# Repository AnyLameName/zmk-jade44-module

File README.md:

# Jade44 - A ZMK Keyboard Module

The Jade44 keyboard is a bespoke keyboard, designed for a userbase of one. 
This repository contains a module for the [ZMK Firmware](https://zmk.dev/) Project that will enable you to build
a firmware for the Jade44.

It also defines a GitHub Actions Workflow that will automatically build the firmware when a change is pushed.

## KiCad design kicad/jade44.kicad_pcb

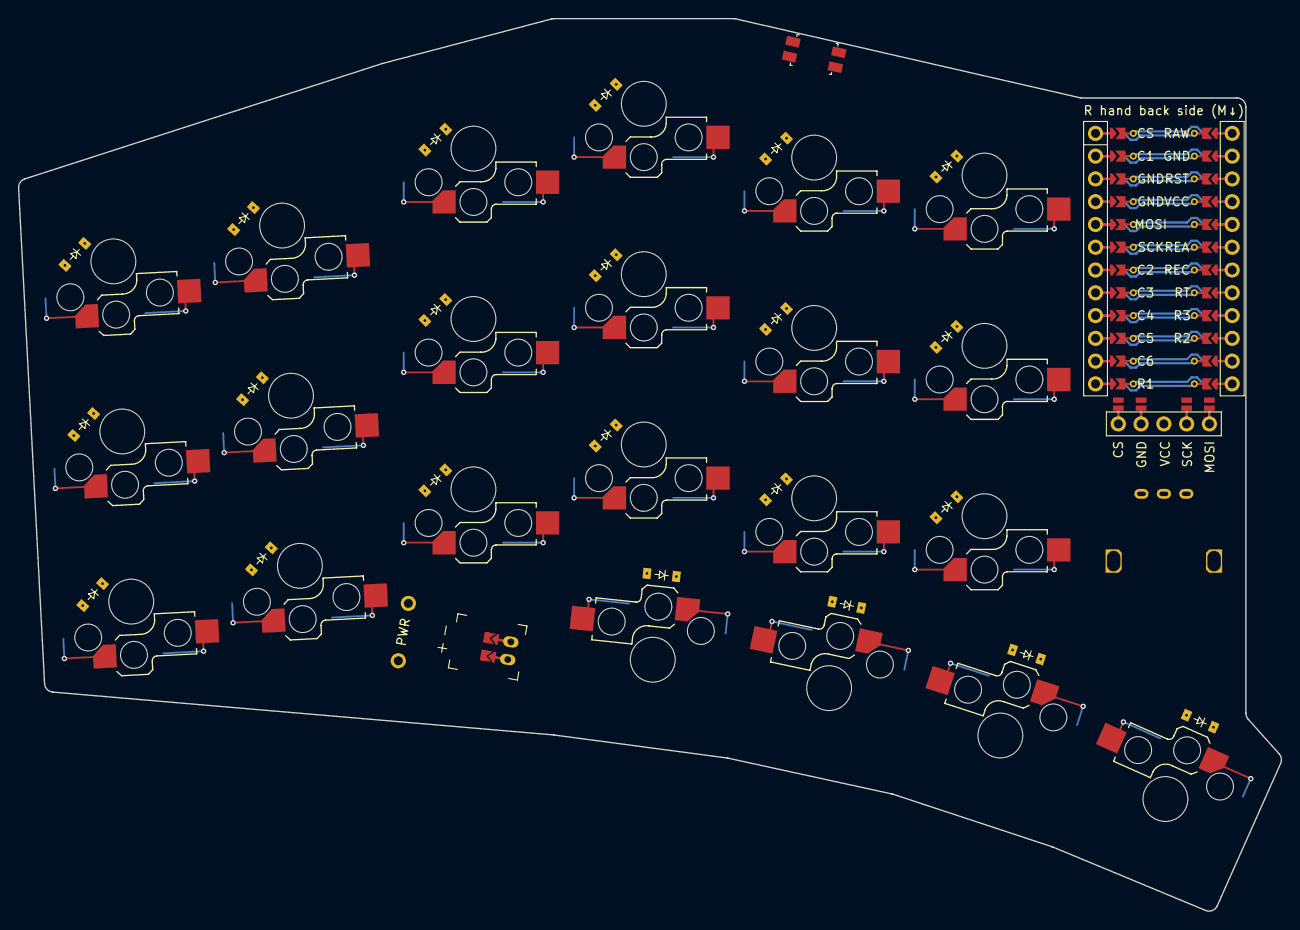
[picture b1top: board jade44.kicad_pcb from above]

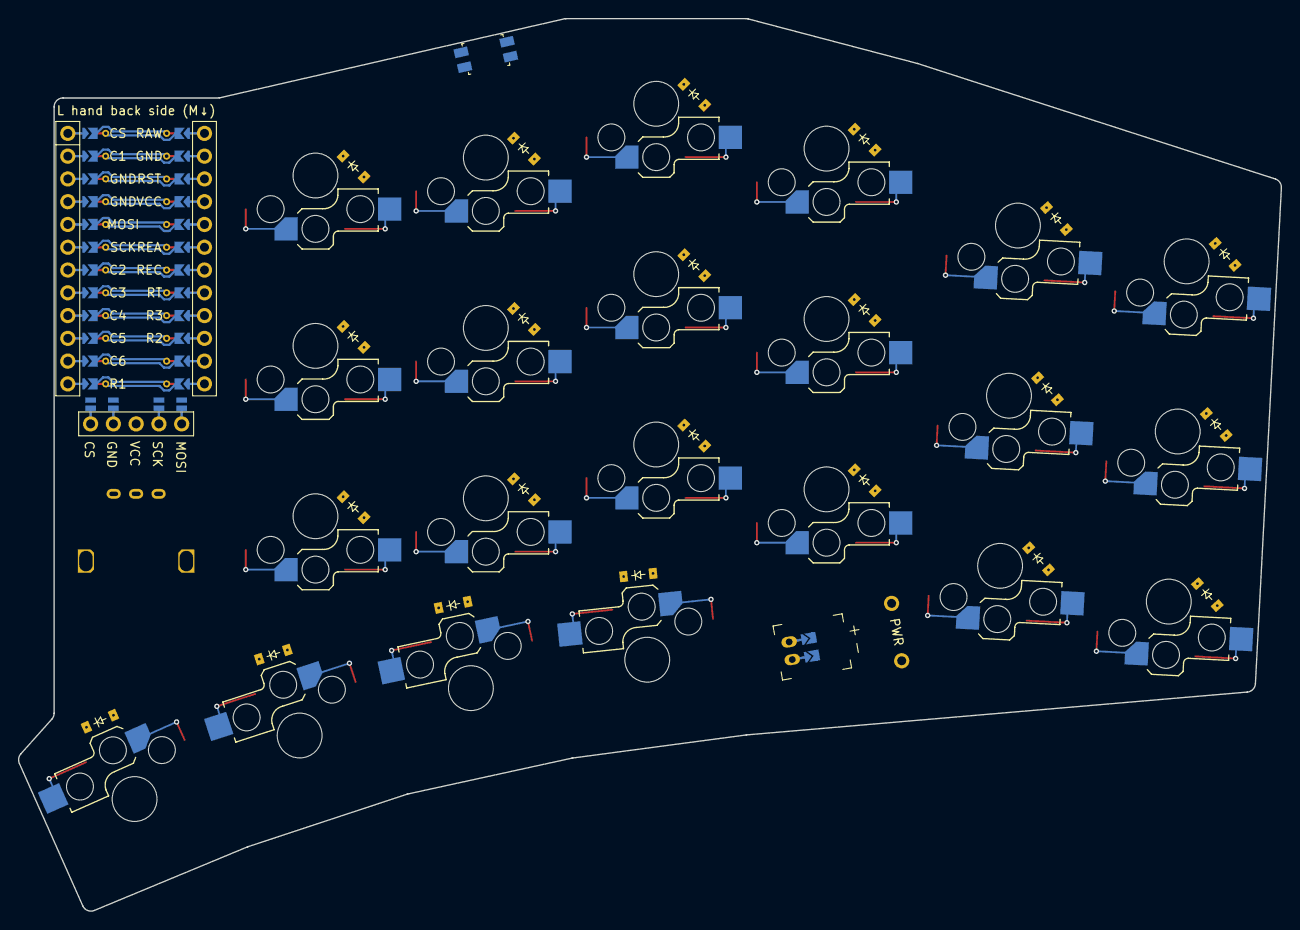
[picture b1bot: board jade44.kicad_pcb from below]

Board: 2 copper layers, 140.8 x 99.5 mm, 50 parts (25 on the bottom side), 48 nets.

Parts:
D1, D2, D3, D4, D5, D6, D7, D8, D9, D10, D11, D12, D13, D14, D15, D16, D17, D18, D19, D20, D21, D22: diode_tht_sod123
DISP1: display_nice_view
JST1: battery_connector_jst_ph_2
MCU1: mcu_nice_nano
PWR1: reset_switch_tht_top
RE1: rotary_encoder_ec11_ec12
RST1: reset_switch_smd_side
S1, S2, S3, S4, S5, S6, S7, S8, S9, S10, S11, S12, S13, S14, S15, S16, S17, S18, S19, S20, S21, S22: switch_choc_v1_v2

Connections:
BAT_P: JST1.1, PWR1.2
C1: MCU1.123, S1.1, S1.2, S2.1, S2.2, S3.1, S3.2
C1_R1: D1.2, S1.1, S1.2
C1_R2: D2.2, S2.1, S2.2
C1_R3: D3.2, S3.1, S3.2
C2: MCU1.118, S4.1, S4.2, S5.1, S5.2, S6.1, S6.2
C2_R1: D4.2, S4.1, S4.2
C2_R2: D5.2, S5.1, S5.2
C2_R3: D6.2, S6.1, S6.2
C3: MCU1.117, S7.1, S7.2, S8.1, S8.2, S9.1, S9.2, S19.1, S19.2
C3_R1: D7.2, S7.1, S7.2
C3_R2: D8.2, S8.1, S8.2
C3_R3: D9.2, S9.1, S9.2
C3_RT: D19.2, S19.1, S19.2
C4: MCU1.116, S10.1, S10.2, S11.1, S11.2, S12.1, S12.2, S20.1, S20.2
C4_R1: D10.2, S10.1, S10.2
C4_R2: D11.2, S11.1, S11.2
C4_R3: D12.2, S12.1, S12.2
C4_RT: D20.2, S20.1, S20.2
C5: MCU1.115, S13.1, S13.2, S14.1, S14.2, S15.1, S15.2, S21.1, S21.2
C5_R1: D13.2, S13.1, S13.2
C5_R2: D14.2, S14.1, S14.2
C5_R3: D15.2, S15.1, S15.2
C5_RT: D21.2, S21.1, S21.2
C6: MCU1.114, S16.1, S16.2, S17.1, S17.2, S18.1, S18.2, S22.1, S22.2
C6_R1: D16.2, S16.1, S16.2
C6_R2: D17.2, S17.1, S17.2
C6_R3: D18.2, S18.1, S18.2
C6_RT: D22.2, S22.1, S22.2
CS: DISP1.14, DISP1.24, MCU1.124
DISP1_1: DISP1.1, DISP1.10, DISP1.23
DISP1_2: DISP1.2, DISP1.11, DISP1.22
DISP1_4: DISP1.4, DISP1.12, DISP1.21
DISP1_5: DISP1.5, DISP1.13, DISP1.20
GND: DISP1.15, DISP1.25, JST1.2, MCU1.102, MCU1.121, MCU1.122, RE1.B, RST1.1, RST1.3
JST1_1: JST1.11, JST1.21, JST1.31
JST1_2: JST1.12, JST1.22, JST1.32
MOSI: DISP1.17, DISP1.27, MCU1.120
R1: D1.1, D4.1, D7.1, D10.1, D13.1, D16.1, MCU1.113
R2: D2.1, D5.1, D8.1, D11.1, D14.1, D17.1, MCU1.110
R3: D3.1, D6.1, D9.1, D12.1, D15.1, D18.1, MCU1.109
RAW: MCU1.101, PWR1.1
REA: MCU1.106, RE1.A
REC: MCU1.107, RE1.C
RST: MCU1.103, RST1.2, RST1.4
RT: D19.1, D20.1, D21.1, D22.1, MCU1.108
SCK: DISP1.16, DISP1.26, MCU1.119
VCC: DISP1.3, MCU1.104

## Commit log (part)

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2025-05-05 Building out starts of 2x2 test module. Needs keymap.
2025-05-23 Fix column offset, add keymap and metadata, create a build.yaml to hopefully get this building.
2025-05-23 The build file doesn't go in the module file.
2025-05-23 Somehow didn't realize I had put all the files next to the jade44 directory instead of in it.
2025-05-23 Copying katori module's module.yml because something is certainly wrong with mine.
2025-05-23 Typo in default_transform
2025-05-23 Need to define a physical layout
2025-05-23 Typo in layout definition.
2025-05-23 Trying to more closely match Corne's configs in an attempt to successfully build.
2025-05-23 Does it not like the label and the struct having the same name?
2025-05-23 Apparently the label property is deprecated for kscan.
2025-05-23 Typo in keymap filename.
2025-05-23 It builds, so let's go back to the original pins. Those weren't the problem.
2025-05-23 Let's try to get the firmware building in this repo instead of a distinct config one.
2025-05-23 Need config directory as well.
2025-05-24 We're having the missing kscan issue again, but that label-struct conflict hasn't regressed, so what is going on here?
2025-05-24 Revert "We're having the missing kscan issue again, but that label-struct conflict hasn't regressed, so what is going on here?"
    This reverts commit b719b7b103b73144b7bfebc7d29e2522206f7481.
2025-05-24 Revert "Let's try to get the firmware building in this repo instead of a distinct config one."
    This reverts commit 99c1a5651cd8dba7bce95ab7be52eab698c1d177.
2025-05-24 Revert "It builds, so let's go back to the original pins. Those weren't the problem."
    This reverts commit e247fdc03ad7bea01bac31a5ad978981a43a4b2f.
2025-05-24 Revert "Need config directory as well."
    This reverts commit 73003ff122dd73ce2285ab93dc60a60de48591ea.
2025-05-24 Small keymap change just to differentiate branches for testing.
2025-05-24 Can we safely move row pins?
2025-05-24 Now move the columns.
2025-05-24 Seems the columns aren't okay? Let's revert the right.
2025-05-25 Testing if struct and label can share a name.
2025-05-25 Second attempt of building firmware in the same repo as the module.
2025-05-25 Not sure why the last build failed, when the PR build succeeded.
2025-05-25 Still had the project defined against the mono-repo branch. That explains it.
2025-05-26 Moving to eight keys, so I will have four keys on a single half. Matrix time!
2025-05-26 Having 8 keys in the matrix and 4 in the keymap isn't super effective.
2025-05-26 Quick README.md change to make it less boilerplate.
2026-06-16 Some new ide/git stuff.
2026-06-21 New 2x3 keyboard layout.
2026-06-22 Pin to zmk v0.3
2026-06-25 Bind a BT Clear button.
2026-06-25 Was the formatting the problem?
2026-06-25 Oh, it was a missing include.
2026-06-25 Enable usb logging.
2026-06-25 Try again on logging.
2026-06-26 Think I had the diode direction wrong.
2026-06-26 Guess not.
2026-06-26 Looks good now. Just had the diodes backwards. No need for a dedicated BT clear right now.
2026-06-26 Turns out you need that a fair bit during early dev work.
2026-06-26 Fix map typo.
2026-06-26 Both halves use the same pinout right now, so column pinouts should be defined in the main devicetree file.
2026-06-26 Maybe blank is better than delete?
2026-06-26 Testing a layer key.
2026-06-26 Put BT_CLR on a chord. Now it is available but not as easy to do by accident.
2026-06-27 Working on the display.
2026-06-27 Switch to built-in screen widget, disable WPM.
